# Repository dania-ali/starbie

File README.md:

# Starbie
A tiny motion controlled digital pet: a desktop tamagotchi that lives on a custom PCB. This version is a Kirby style pet that wanders a small OLED and reacted when ypu shake/tilt the board. It likes to stargaze when nothing is going on.

Built for Hack Club's Half-Life

# What it is
Starbie sits on your desk and shows its personality through the sall display. It also reacts to how you handle it. You can interact with it by oving the board. The board has a microcontroller, display, motion sensor, and environmental sensor in its PCB design. 

# What it does
- Wanders across the screen as a 32x32 px Kirby
- Radial menu: press Button 1, tilt the board as a selector ball, then press Button 1 again to pick an action. Each action changes the pet's stats
- Stats screen: Button 2 to see joy, energy, fullness
- Shake reaction: shake the board

# Cool features
- Sparkle trail behind the Starbie when it walks
- Idle stargazing: after 15 sec with no activity, Starbie stops and twinkling stars appear above it
- Custom Kirby sprite

# Hardware
- Seeed XIAO ESP32-C3:	Microcontroller
- SSD1306 128x64 OLED (I2C): Display
- MPU6050:	Motion sensor for the tilt menu and shake
- DHT11:	Temperature and humidity
- 2x tactile buttons:	Menu and stats

# Controls
- Button 1 (first press):	Open the radial menu
- Tilt (menu open):	Move the selector ball
- Button 1 (second press):	Choose the highlighted action
- Button 2:	Show or hide the stats screen
- Shake:	Starbie wiggles

# Software
Firmware/ contains one Arduino IDE sketch for the microcontroller. All settings are at the top. 

# Case (CAD)
Starbie lives in a custom star-shaped, two-part case designed in Onshape around the PCB (imported from KiCad as a STEP file). Files are in CAD/.

# Repo contents
- PCB/ - KiCad source files, schematic PDF, and fabrication exports (Starbie-gerbers.zip)
- Firmware/ - Arduino IDE sketch (Starbie/Starbie.ino)
- CAD/ - Case step files

# Credits
- Hack Club Half-Life Starbie guide as starting point
- Kirby is a character owned by Nintendo. This is a personal, non-commercial fan project.

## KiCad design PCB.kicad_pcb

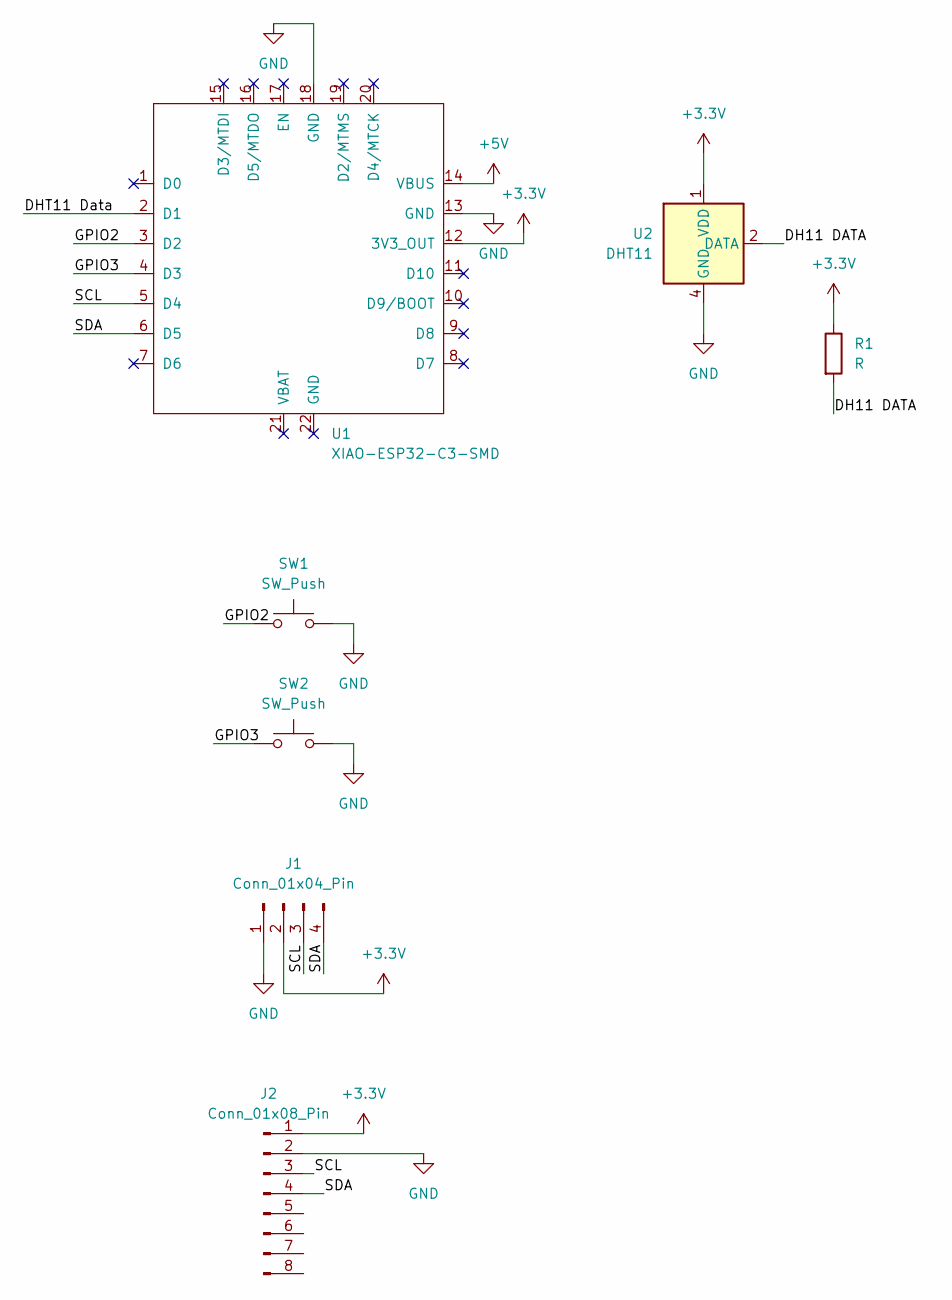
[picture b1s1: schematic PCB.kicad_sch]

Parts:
J1: Conn_01x04_Pin; Display_128x64_096_I2C
J2: Conn_01x08_Pin; PinHeader_1x08_P2.54mm_Vertical
R1: R; R_Axial_DIN0204_L3.6mm_D1.6mm_P7.62mm_Horizontal
SW1, SW2: SW_Push; SW_Cherry_MX_1.00u_PCB
U1: XIAO-ESP32-C3-SMD
U2: DHT11; Aosong_DHT11_5.5x12.0_P2.54mm

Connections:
+3.3V: J1.2, J2.1, R1.1, U1.12 (3V3_OUT), U2.1 (VDD)
+5V: U1.14 (VBUS)
/DH11 DATA: R1.2, U2.2 (DATA)
/DHT11 Data: U1.2 (D1)
/GPIO2: SW1.1, U1.3 (D2)
/GPIO3: SW2.1, U1.4 (D3)
/SCL: J1.3, J2.3, U1.5 (D4)
/SDA: J1.4, J2.4, U1.6 (D5)
GND: J1.1, J2.2, SW1.2, SW2.2, U1.13 (GND), U1.18 (GND), U2.4 (GND)

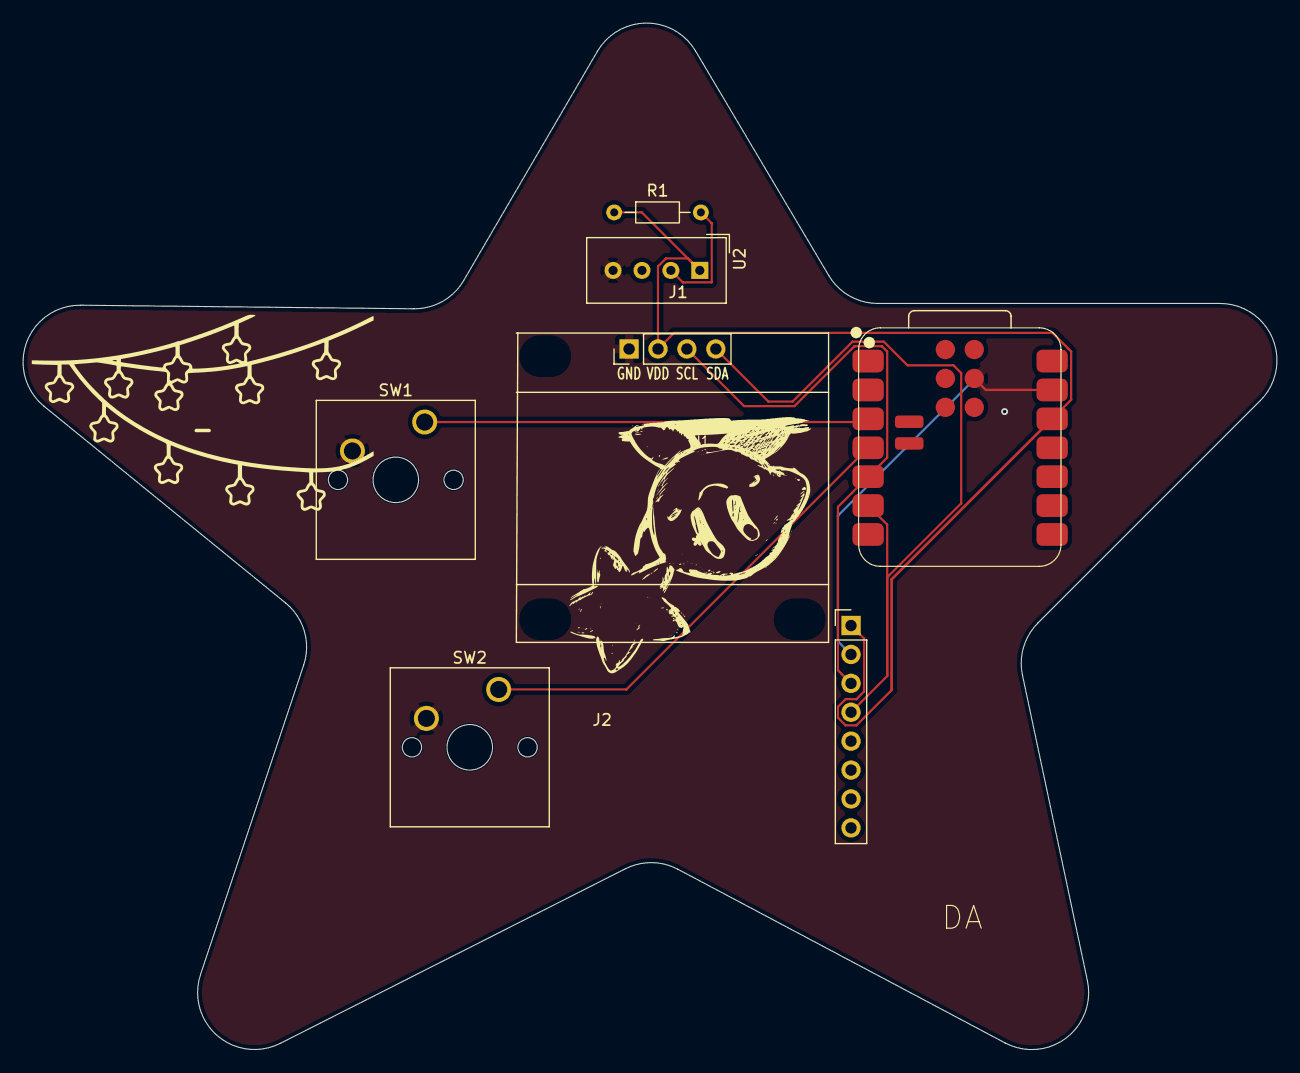
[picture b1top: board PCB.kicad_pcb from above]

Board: 2 copper layers, 110.2 x 90.2 mm, 9 parts (0 on the bottom side), 7 nets.

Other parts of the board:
*: LOGO
-: LOGO
